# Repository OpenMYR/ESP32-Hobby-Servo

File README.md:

# ESP32-Hobby-Servo
Open MYR ESP32 controller board, 15 port servo direct

Use with [ESP32-Motors](https://github.com/OpenMYR/ESP32-Motors) or write your own firmware.

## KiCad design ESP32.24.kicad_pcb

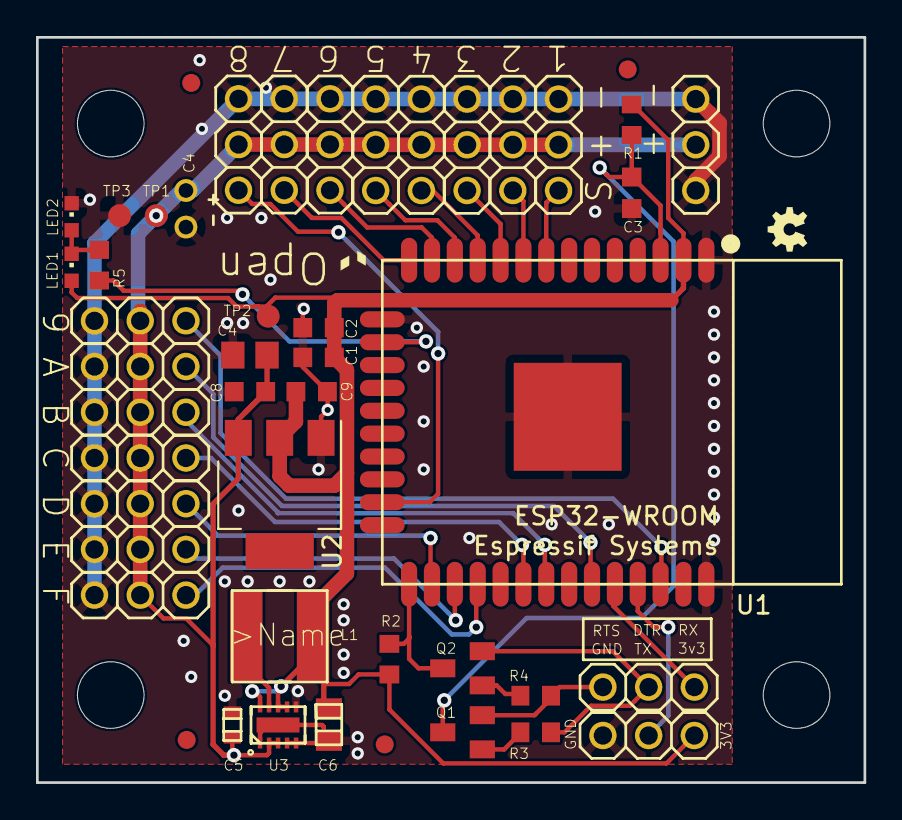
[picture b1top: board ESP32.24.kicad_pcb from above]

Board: 2 copper layers, 46.0 x 41.4 mm, 52 parts (0 on the bottom side), 29 nets.

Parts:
C1, C3: 0.1uF; C0603K
C2, C8, C9: 10uF; C0603K
C4: DNP; E2-4
C5: GRM188R61C225KE15D; 0603
C6: GRM21BR60J226ME39L; 0805
C7: DNP; C0805
H1, H2, H3, H4: MOUNT-HOLE3.6; MountingHole_3.7mm
J1, J2, J3, J4, J5, J6, J7, J8, J9, J10, J11, J12, J13, J14, J15, J16, J17, J18: Conn_01x03_Male; 1X03
L1: SDR0503-100ML; SDR0503
LED1, LED2: DNP; CHIPLED_0603
LOGO1: OSHW-LOGOMINI; OSHW-LOGO-MINI
Q1, Q2: MMBT3904; SOT23
R1, R2, R3, R4: 10k; R0603
R5: DNP; R0603
TP1, TP2, TP3: PTR1B1,27; B1,27
U1: ESP32-WROOM
U2: AZ1117-3.3; SOT-223
U3: TPS62177DQCR; R-PWSON-N10
U$1, U$6, U$10, U$11: FIDUCIAL; FIDUCIAL_1MM

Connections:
+3V3: C1.1, C2.1, C6.2, C9.1, J1.1, L1.2, LED1.A, R1.2, R2.2, TP2.TP, U1.2, U2.2, U3.7, U3.8, U3.10
+6V: C4.+, C5.2, C7.1, C8.1, J3.2, J4.2, J5.2, J6.2, J7.2, J8.2, J9.2, J10.2, J11.2, J12.2, J13.2, J14.2, J15.2, J16.2, J17.2, J18.2, TP1.TP, U2.3, U3.2, U3.3
/DTR: J2.2, Q2.2, R3.1
/GPIO0: Q2.3, R2.1, U1.25
/GPIO4: J16.1, U1.26
/GPIO12: J10.1, U1.14
/GPIO13: R5.1, U1.16
/GPIO14: J9.1, U1.13
/GPIO15: J11.1, U1.23
/GPIO16: J17.1, U1.27
/GPIO17: J18.1, U1.28
/GPIO18: J15.1, U1.30
/GPIO19: J14.1, U1.31
/GPIO21: J13.1, U1.33
/GPIO22: J12.1, U1.36
/GPIO25: J6.1, U1.10
/GPIO26: J7.1, U1.11
/GPIO27: J8.1, U1.12
/GPIO32: J4.1, U1.8
/GPIO33: J5.1, U1.9
/RESET: C3.1, Q1.3, R1.1, U1.3
/RTS: J2.1, Q1.2, R4.1
/RXD: J2.3, U1.34
/TXD: J1.2, U1.35
GND: C1.2, C2.2, C3.2, C4.-, C5.1, C6.1, C7.2, C8.2, C9.2, J1.3, J3.1, J3.3, J4.3, J5.3, J6.3, J7.3, J8.3, J9.3, J10.3, J11.3, J12.3, J13.3, J14.3, J15.3, J16.3, J17.3, J18.3, LED2.C, TP3.TP, U1.1, U1.15, U1.38, U1.39, U2.1, U3.1, U3.4, U3.5, U3.6, U3.11
unnamed: L1.1, U3.9
unnamed: LED1.C, LED2.A, R5.2
unnamed: Q1.1, R3.2
unnamed: Q2.1, R4.2

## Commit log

2020-04-19 Open MYR ESP32 fifteen port Hobby Servo control board
    Board designed on KiCAD 5.
    Uses ESP32 KiCAD library from https://github.com/adamjvr/ESP32-kiCAD-Footprints
2020-04-19 Added footprint library folder used.
2020-07-08 Addition of schematic

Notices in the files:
ESP32.24.kicad_pcb:
Copyright Open MYR, LLC 2020.
Licensed under CERN OHL v.1.2 or later
